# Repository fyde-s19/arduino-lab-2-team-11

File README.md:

# arduino-lab-2-team-11
arduino-lab-2-team-11 created by GitHub Classroom
1. The dimmer decreases the duty cycle of the LED and we see a rapid changing in the LED state (ON, OFF, ON, OFF). 
Took about 1.4 seconds for a full cycle, ~.1 seconds to execute Read Sensors?
Advatange of logic analyzer debugging, multiple channels, can read different sorts of signals, reads time for signals, can operate like an osciloscope
Advatanges of serial monitor debugging: its convenient, already built into the program (at least in this case), can easily read pin data.
When measuring the voltages, we need to minimize variance in ground levels so that they are giving an accurate relative voltage measurement.

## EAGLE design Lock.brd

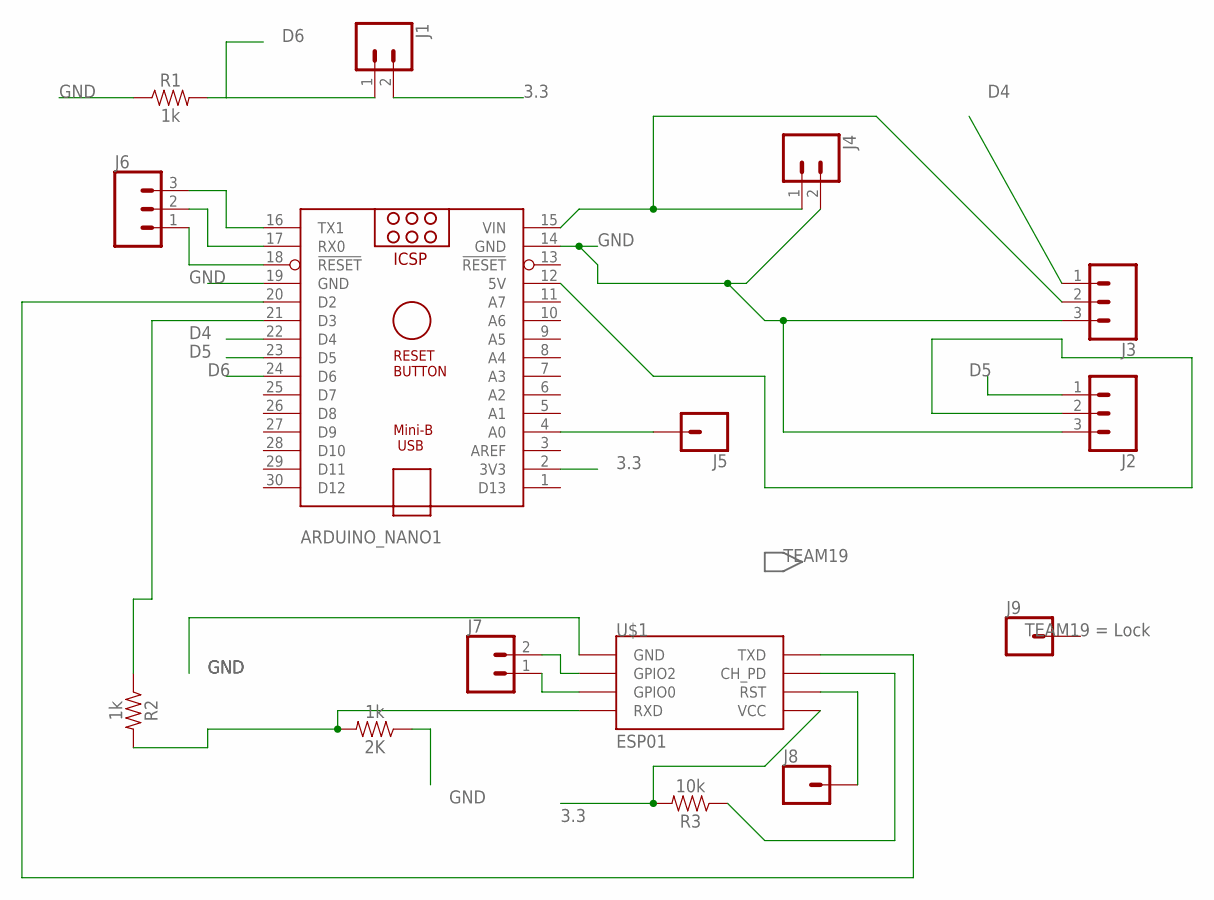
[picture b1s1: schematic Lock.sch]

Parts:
2K: 1k; AXIAL-0.3
ARDUINO_NANO1: ARDUINO_NANO
J1, J4, J7: CONN_02; 1X02
J2, J3, J6: CONN_03; 1X03
J5, J8, J9: CONN_01; 1X01
R1, R2: 1k; AXIAL-0.3
R3: 10k; AXIAL-0.3
U$1: ESP01

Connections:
3.3: ARDUINO_NANO1.2 (3V3), J1.2, R3.P$2 (2), U$1.VCC
D4: ARDUINO_NANO1.22 (D4), J3.1
D5: ARDUINO_NANO1.23 (D5), J2.1
D6: ARDUINO_NANO1.24 (D6), J1.1, R1.P$2 (2)
GND: 2K.P$1 (1), ARDUINO_NANO1.14 (GND), ARDUINO_NANO1.19 (GND), J2.3, J3.3, J4.2, R1.P$1 (1), U$1.GND
unnamed: ARDUINO_NANO1.20 (D2), U$1.TX (TXD)
unnamed: 2K.P$2 (2), R2.P$2 (2), U$1.RX (RXD)
unnamed: ARDUINO_NANO1.21 (D3), R2.P$1 (1)
unnamed: R3.P$1 (1), U$1.CH_PD
unnamed: ARDUINO_NANO1.4 (A0), J5.1
unnamed: ARDUINO_NANO1.15 (VIN), J3.2, J4.1
unnamed: J7.2, U$1.GPIO2
unnamed: J7.1, U$1.GPIO0
unnamed: J8.1, U$1.RST
unnamed: ARDUINO_NANO1.18 (!RESET), J6.1
unnamed: ARDUINO_NANO1.17 (RX0), J6.2
unnamed: ARDUINO_NANO1.16 (TX1), J6.3
unnamed: ARDUINO_NANO1.12 (5V), J2.2

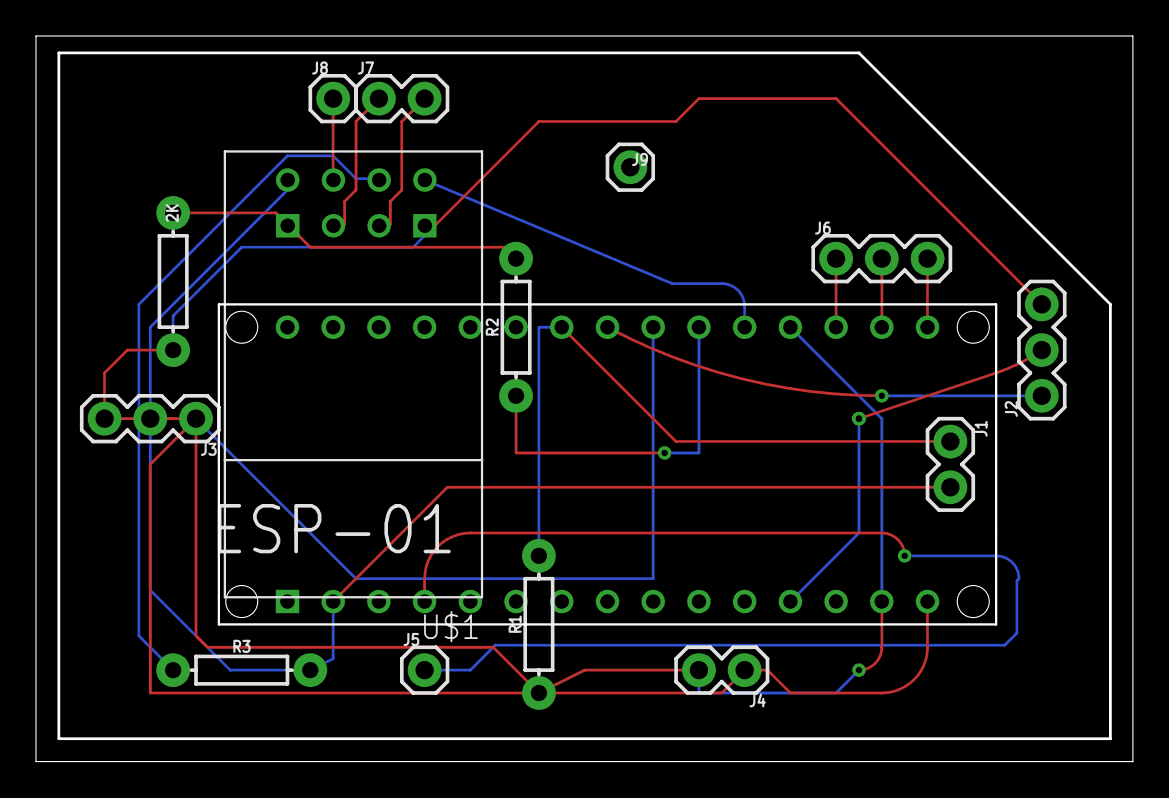
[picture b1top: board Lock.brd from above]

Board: 2 copper layers, 60.8 x 40.2 mm, 15 parts (0 on the bottom side), 18 nets.

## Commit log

2019-03-06 just followed the lab doc, make sure you have your board set to the mega
2019-05-03 Correct code in c file
2019-05-03 Code should be ready
2019-05-03 Uncertain about the pin to be attached

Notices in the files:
parts and their libraries:
SparkFun-Resistors: Licensing: Creative Commons ShareAlike 4.0 International - https://creativecommons.org/licenses/by-sa/4.0
dports: Copyright (C) 2005, Bob Starr (bobstarr@mindspring.com)
